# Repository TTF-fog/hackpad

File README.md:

# hackpad!!
a simple 9-key macropad with backlighting

# Why
- ...i've never made one before
- i did actually need a macropad
- i wanted to use a ribbon connector but didn't have anything that needed one
- i needed to remember how to CAD

# Sub(Links)
- [Zine.pdf](zine.pdf)
- [Design](design/)
- [BOM](BOM.csv)
- [Gerbers](gerbers.zip) 
- [Schematic PDF](design/hackpad.pdf)

> DO FLASHING BEFORE ASSEMBLY!
# flashing
- make sure you have QMK installed
- copy the firmware/firmware directory into the keyboards directory of your qmk installation
- run qmk compile -kb wackpad -km default
- on the xiao, ground the BOOT pad while plugging it into the computer
- drop the resultant .uf2 from the previous previous (englishj) step into the flash drive
- after the copying is done (may take a while), the drive will automatically eject
# hardware assembly
- solder the components
- print the case
- place the pcb in the case so the mounting holes go through the stands
- align the OLED ribbon to go through the display hole
- assembly done!

# images

> PCB

>Schematic

> the CAD

> zine img

>pcb 3dview

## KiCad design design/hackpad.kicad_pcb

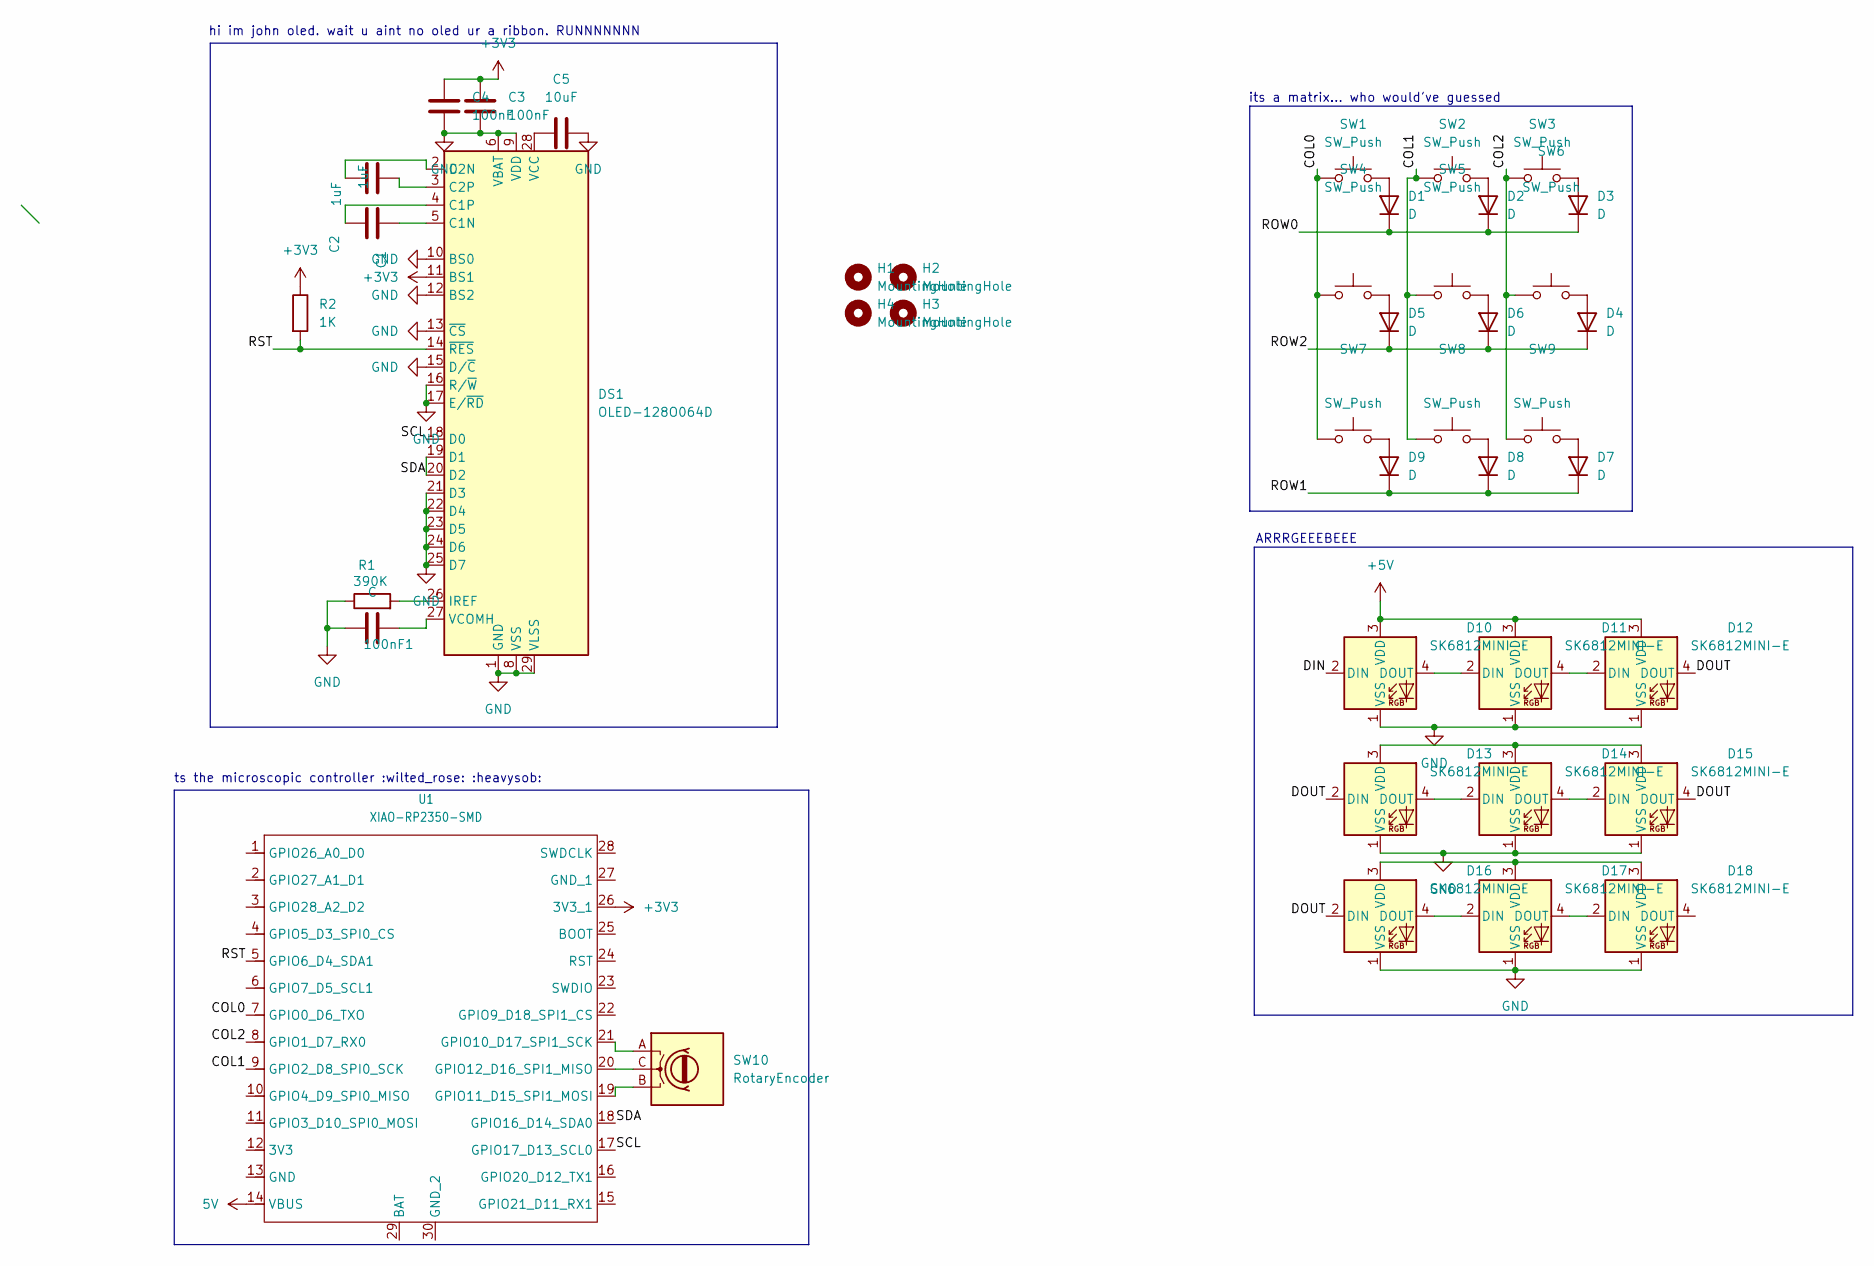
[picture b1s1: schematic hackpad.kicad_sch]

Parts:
100nF1: C; C_0402_1005Metric
C1, C2: 1uF; C_0402_1005Metric
C3, C4: 100nF; C_0402_1005Metric
C5: 10uF; C_0402_1005Metric
D1, D2, D3, D4, D5, D6, D7, D8, D9: D; D_0603_1608Metric_Pad1.05x0.95mm_HandSolder
D10, D11, D12, D13, D14, D15, D16, D17, D18: SK6812MINI-E; LED_SK6812MINI_PLCC4_3.5x3.5mm_P1.75mm
DS1: OLED-128O064D
H1, H2, H3, H4: MountingHole; MountingHole_2.1mm
R1: 390K; R_0402_1005Metric
R2: 1K; R_0402_1005Metric
SW1, SW2, SW3, SW4, SW5, SW6, SW7, SW8, SW9: SW_Push; SW_Cherry_MX_1.00u_PCB
SW10: RotaryEncoder; RotaryEncoder_Alps_EC11E-Switch_Vertical_H20mm
U1: XIAO-RP2350-SMD

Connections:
5V: U1.14 (VBUS)
+3V3: C3.1, C4.1, DS1.11 (BS1), R2.1, U1.26 (3V3_1)
+5V: D10.3 (VDD), D11.3 (VDD), D12.3 (VDD)
/COL0: SW1.1, SW4.1, SW7.1, U1.7 (GPIO0_D6_TXO)
/COL1: SW2.1, SW5.1, SW8.1, U1.9 (GPIO2_D8_SPI0_SCK)
/COL2: SW3.1, SW6.1, SW9.1, U1.8 (GPIO1_D7_RX0)
/DIN: D10.2 (DIN)
/DOUT: D12.4 (DOUT), D13.2 (DIN), D15.4 (DOUT), D16.2 (DIN)
/ROW0: D1.1 (K), D2.1 (K), D3.1 (K)
/ROW1: D7.1 (K), D8.1 (K), D9.1 (K)
/ROW2: D4.1 (K), D5.1 (K), D6.1 (K)
/RST: DS1.14 (~RES), R2.2, U1.5 (GPIO6_D4_SDA1)
/SCL: DS1.18 (D0), U1.17 (GPIO17_D13_SCL0)
/SDA: DS1.19 (D1), DS1.20 (D2), U1.18 (GPIO16_D14_SDA0)
GND: 100nF1.2, C3.2, C4.2, C5.2, D10.1 (VSS), D11.1 (VSS), D12.1 (VSS), D13.1 (VSS), D14.1 (VSS), D15.1 (VSS), D16.1 (VSS), D17.1 (VSS), D18.1 (VSS), DS1.1 (GND), DS1.6 (VBAT), DS1.8 (VSS), DS1.9 (VDD), DS1.10 (BS0), DS1.12 (BS2), DS1.13 (~CS), DS1.15 (D/~C), DS1.16 (R/~W), DS1.17 (E/~RD), DS1.21 (D3), DS1.22 (D4), DS1.23 (D5), DS1.24 (D6), DS1.25 (D7), DS1.29 (VLSS), DS1.30 (GND), R1.1
unnamed: D1.2 (A), SW1.2
unnamed: D2.2 (A), SW2.2
unnamed: D3.2 (A), SW3.2
unnamed: D4.2 (A), SW6.2
unnamed: D5.2 (A), SW4.2
unnamed: D6.2 (A), SW5.2
unnamed: D7.2 (A), SW9.2
unnamed: D8.2 (A), SW8.2
unnamed: D9.2 (A), SW7.2
unnamed: D10.4 (DOUT), D11.2 (DIN)
unnamed: D11.4 (DOUT), D12.2 (DIN)
unnamed: D13.4 (DOUT), D14.2 (DIN)
unnamed: D13.3 (VDD), D14.3 (VDD), D15.3 (VDD)
unnamed: D14.4 (DOUT), D15.2 (DIN)
unnamed: D16.4 (DOUT), D17.2 (DIN)
unnamed: D16.3 (VDD), D17.3 (VDD), D18.3 (VDD)
unnamed: D17.4 (DOUT), D18.2 (DIN)
unnamed: C1.1, DS1.5 (C1N)
unnamed: C1.2, DS1.4 (C1P)
unnamed: C2.1, DS1.2 (C2N)
unnamed: C2.2, DS1.3 (C2P)
unnamed: DS1.26 (IREF), R1.2
unnamed: C5.1, DS1.28 (VCC)
unnamed: 100nF1.1, DS1.27 (VCOMH)
unnamed: SW10.A, U1.21 (GPIO10_D17_SPI1_SCK)
unnamed: SW10.B, U1.19 (GPIO11_D15_SPI1_MOSI)
unnamed: SW10.C, U1.20 (GPIO12_D16_SPI1_MISO)

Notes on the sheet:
hi im john oled. wait u aint no oled ur a ribbon. RUNNNNNNN
its a matrix... who would've guessed
ts the microscopic controller :wilted_rose: :heavysob:
ARRRGEEEBEEE

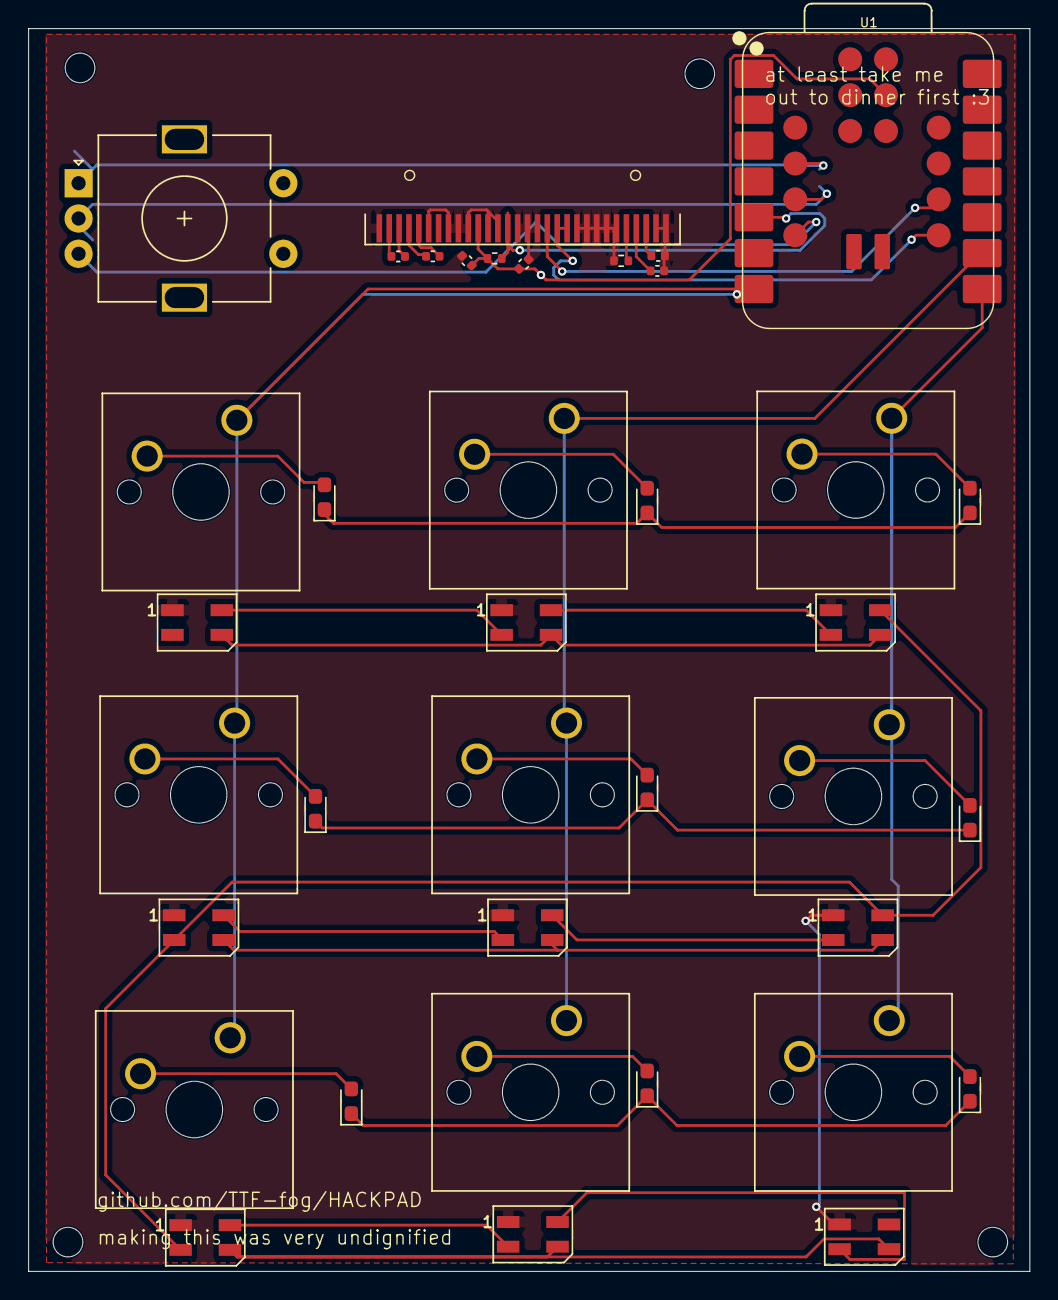
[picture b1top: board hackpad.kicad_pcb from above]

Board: 2 copper layers, 70.9 x 88.0 mm, 42 parts (0 on the bottom side), 40 nets.

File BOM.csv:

Comment,Designator,Footprint,LCSC,Quantity,Link,Price/Unit,Price (Total)
100nF,"C3,C4",C_0402_1005Metric,C1525,2,https://lcsc.com/product-detail/C1525.html,0.0031,0.31
10uF,C5,C_0402_1005Metric,C15525,1,https://lcsc.com/product-detail/C15525.html,0.0199,1.99
1K,R2,R_0402_1005Metric,C11702,1,https://lcsc.com/product-detail/C11702.html,0.0011,0.11
1uF,"C1,C2",C_0402_1005Metric,C52923,2,https://lcsc.com/product-detail/C52923.html,0.0143,0.72
390K,R1,R_0402_1005Metric,C25557,1,https://lcsc.com/product-detail/C25557.html,0.0007,0.07
C,100nF1,C_0402_1005Metric,C1525,1,https://lcsc.com/product-detail/C1525.html," 0.0031
",0.31
D,"D1,D2,D3,D4,D5,D6,D7,D8,D9",D_SOD-323,N/A,9,https://robu.in/product/1n4148ws-7-f-diodes-incorporated-75v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,0.05,0.45
SK6812MINI-E,"D10,D11,D12,D13,D14,D15,D16,D17,D18",LED_SK6812MINI_PLCC4_3.5x3.5mm_P1.75mm,C5149201,9,https://lcsc.com/product-detail/C5149201.html,0.0876,0.7884
SW_Push,"SW1,SW2,SW3,SW4,SW5,SW6,SW7,SW8,SW9",SW_Cherry_MX_1.00u_PCB,N/A,9,https://meckeys.com/shop/accessories/keyboard-accessories/ke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,0.46,4.6
RotaryEncoder,SW10,RotaryEncoder_Alps_EC11E-Switch_Vertical_H20mm,N/A,1,https://robu.in/product/hongyan-ec11h-7ce20p1zy20-rotary-enc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,0.58,0.58
XIAO-RP2350-SMD,U1,XIAO-RP2350-SMD,N/A,1,https://robu.in/product/seeedstudio-xiao-rp2350-raspberry-pi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,8.4,8.4
OLED-128O064D,DS1,OLED-128O064D,N/A,1,https://robu.in/product/oled-with-ssd1306/,1.6,1.6
PCB Milling,N/A,N/A,N/A,1,https://jlcpcb.com,2,2
,,,,,,13.2167,21.9284

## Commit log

2026-06-20 ADD FIRST
2026-06-20 remove ss trext
2026-06-20 push ze firmware!!!!
2026-06-20 add firmware, forgor to add the 5v net
2026-06-20 juhn
2026-06-20 updatre hackpad, add assemblie(s)
2026-06-20 wumbus
2026-06-20 update quicklinks, add schmematic pdf
2026-06-20 add more silkscreen tezt
2026-06-24 change
2026-06-24 update step file
2026-06-24 add cad pictre
2026-06-24 add new zine
2026-06-24 bingus
2026-06-24 done!
